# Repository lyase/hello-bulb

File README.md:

as of october 2015
I think  master branch is broken  with
device:  device_plan.pro
firmware: /home/ubsafder/work/hello-bulb/firmware/usbtiny-1.7/usb-device-standalone-firmware/

so i am making a new branch now based on the work https://www.obdev.at/products/vusb/prjdetail.php?pid=0
the new board is power-switch.pro
and the firmware are found in /PowerSwitchobdev/
to be tested in real world

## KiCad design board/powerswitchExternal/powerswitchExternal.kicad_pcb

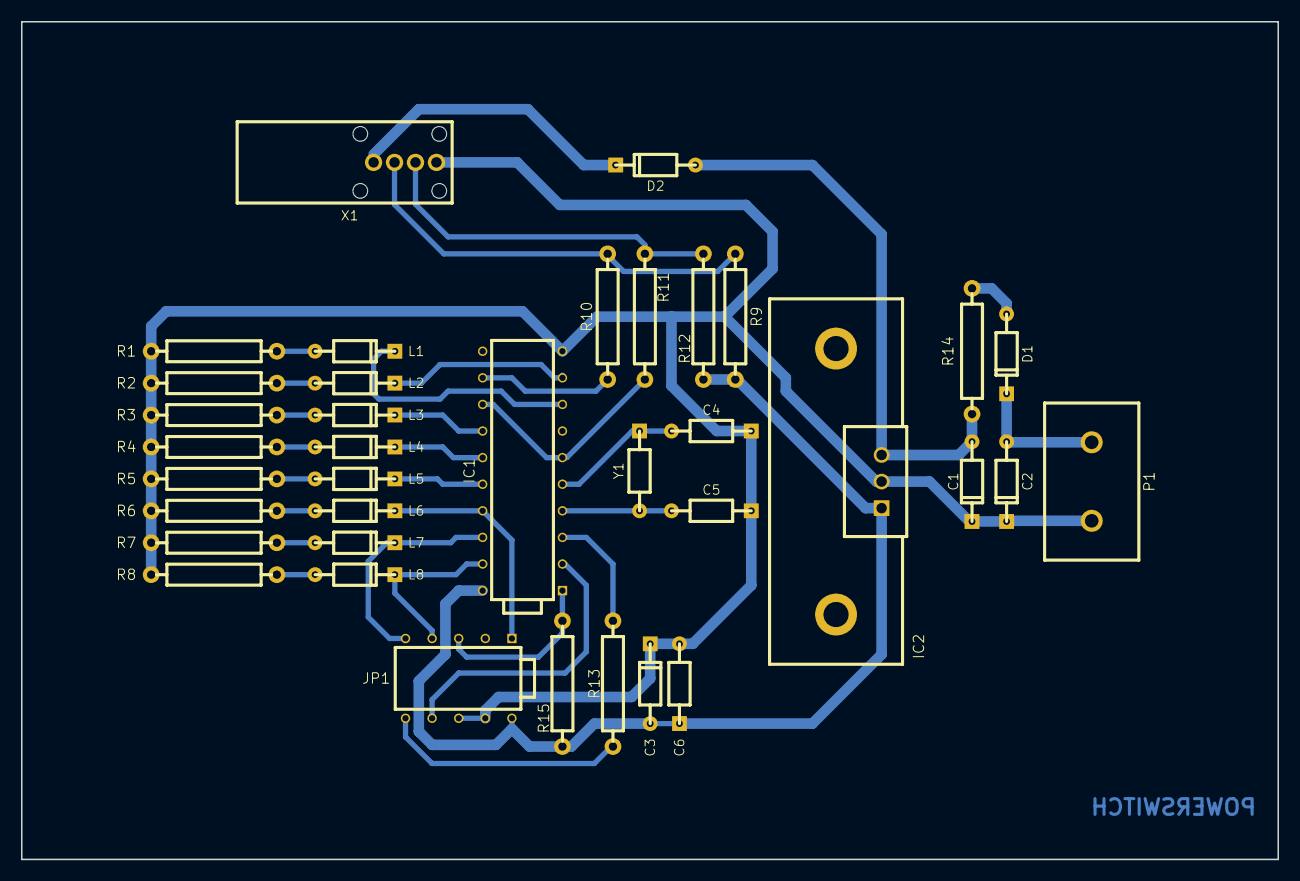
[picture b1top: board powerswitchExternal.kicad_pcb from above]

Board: 2 copper layers, 120.0 x 80.0 mm, 37 parts (0 on the bottom side), 32 nets.

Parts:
C1: 10u/16V; PT-DO35
C2: 1000u/16V; PT-DO35
C3: 2u2/16V; PT-DO35
C4, C5: 15p; PT-CAP
C6: 100n; PT-CAP
D1, D2: 1N4148; PT-DO35
IC1: AT90S2313-P; PT-PDIP20
IC2: LE35CZ; PT-TO220AB
JP1: CONN_02X05; PT-PDIP10
L1, L2, L3, L4, L5, L6, L7, L8: LED; PT-DO35
P1: 12V DC; PT-CONN2-7.5mm
R1, R2, R3, R4, R5, R6, R7, R8: 1K; R7
R9: 1K5; R7
R10, R11: 68R; R7
R12: 1M; R7
R13, R15: 10K; R7
R14: 330R; R7
X1: USB; PT-TE292336
Y1: 12MHz; PT-CAP

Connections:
GND: C1.2, C2.2, C3.2, C4.2, C5.2, C6.1, IC1.10, IC2.2, JP1.4, JP1.6, P1.2, R1.2, R2.2, R3.2, R4.2, R5.2, R6.2, R7.2, R8.2, X1.4
unnamed: C1.1, D2.1, IC2.3, R14.2
unnamed: C2.1, D1.2, P1.1
unnamed: C3.1, C6.2, IC1.20, IC2.1, JP1.2, R9.1, R12.1, R15.1
unnamed: C4.1, IC1.5, Y1.2
unnamed: C5.1, IC1.4, Y1.1
unnamed: D1.1, R14.1
unnamed: D2.2, X1.1
unnamed: IC1.1, JP1.5, R15.2
unnamed: IC1.2, JP1.8
unnamed: IC1.3, R13.1
unnamed: IC1.8, L1.2
unnamed: IC1.9, L2.2
unnamed: IC1.12, R10.1
unnamed: IC1.6, IC1.13, R11.1
unnamed: IC1.14, L3.2
unnamed: IC1.15, L4.2
unnamed: IC1.16, L5.2
unnamed: IC1.17, JP1.1, L6.2
unnamed: IC1.18, JP1.9, L7.2
unnamed: IC1.19, JP1.7, L8.2
unnamed: JP1.10, R13.2
unnamed: L1.1, R1.1
unnamed: L2.1, R2.1
unnamed: L3.1, R3.1
unnamed: L4.1, R4.1
unnamed: L5.1, R5.1
unnamed: L6.1, R6.1
unnamed: L7.1, R7.1
unnamed: L8.1, R8.1
unnamed: R9.2, R10.2, X1.2
unnamed: R11.2, R12.2, X1.3

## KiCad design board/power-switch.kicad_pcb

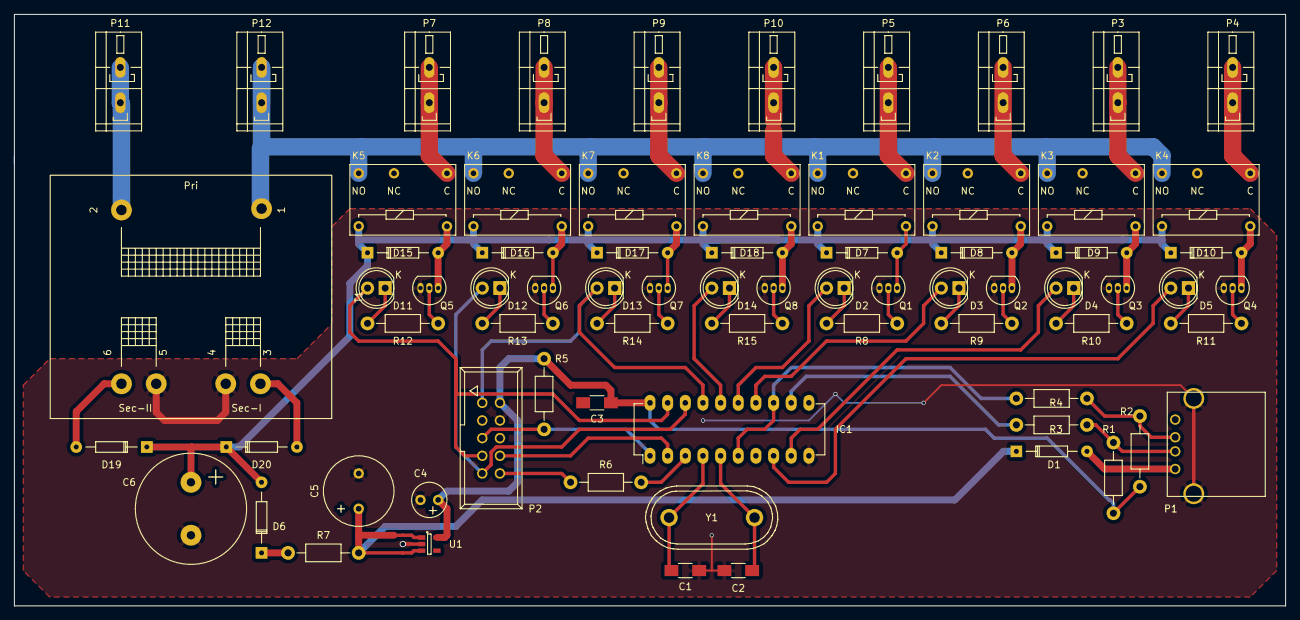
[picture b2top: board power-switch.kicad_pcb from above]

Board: 2 copper layers, 182.9 x 85.1 mm, 73 parts (0 on the bottom side), 60 nets.

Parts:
C1, C2, C3: 15pF; C_1206_HandSoldering
C4: 2u2/16V; Elko_vert_11x5mm_RM2.5
C5: 10uF/16V; Elko_vert_20x10mm_RM5
C6: 1000uF/16V; Elko_vert_31.5x16mm_RM7.5
D1, D6, D7, D8, D9, D10, D15, D16, D17, D18: 1N4148; Diode_DO-35_SOD27_Horizontal_RM10
D2, D3, D4, D5, D11, D12, D13, D14: LED; LED-5MM
D19, D20: 1N4004; Diode_DO-35_SOD27_Horizontal_RM10
IC1: AT90S2313-P; DIP-20_W7.62mm_LongPads
K1, K2, K3, K4, K5, K6, K7, K8: RELAY; Relay_SPDS_OMRON-G6E
P1: USB_A
P2: CONN_02X05; VASCH5x2
P3, P4, P5, P6, P7, P8, P9, P10, P11, P12: TEST; TerminalBlock_WAGO-236_2Stift_RM5mm_1pol
Q1, Q2, Q3, Q4, Q5, Q6, Q7, Q8: BC547; TO-92_Inline_Narrow_Oval
R1: 1K5; Resistor_Horizontal_RM10mm
R2: 1M; Resistor_Horizontal_RM10mm
R3, R4: 68R; Resistor_Horizontal_RM10mm
R5, R6: 10K; Resistor_Horizontal_RM10mm
R7: 330R; Resistor_Horizontal_RM10mm
R8, R9, R10, R11, R12, R13, R14, R15: 1K; Resistor_Horizontal_RM10mm
T1: TRANSFO2; Trafo_CHK-EI38-3VA_2xSec
U1: TLV70235DBV; SOT-23-5
Y1: Crystal; Crystal_HC48-U_Vertical

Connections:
GND: C1.1, C2.1, C4.2, C5.2, C6.2, IC1.10, P1.5, P2.4, P2.6, Q1.3, Q2.3, Q3.3, Q4.3, Q5.3, Q6.3, Q7.3, Q8.3, T1.4, T1.5, U1.2
unnamed: C1.2, IC1.4, Y1.1
unnamed: C2.2, IC1.5, Y1.2
unnamed: C5.1, D1.1, R7.1, U1.1, U1.3
unnamed: C6.1, D6.2, D7.1, D8.1, D9.1, D10.1, D15.1, D16.1, D17.1, D18.1, D19.1, D20.1, K1.8, K2.8, K3.8, K4.8, K5.8, K6.8, K7.8, K8.8
unnamed: D1.2, P1.1
unnamed: D2.1, R8.2
unnamed: D3.1, R9.2
unnamed: D4.1, R10.2
unnamed: D5.1, R11.2
unnamed: D6.1, R7.2
unnamed: D7.2, K1.9, Q1.1
unnamed: D8.2, K2.9, Q2.1
unnamed: D9.2, K3.9, Q3.1
unnamed: D10.2, K4.9, Q4.1
unnamed: D11.1, R12.2
unnamed: D12.1, R13.2
unnamed: D13.1, R14.2
unnamed: D14.1, R15.2
unnamed: D15.2, K5.9, Q5.1
unnamed: D16.2, K6.9, Q6.1
unnamed: D17.2, K7.9, Q7.1
unnamed: D18.2, K8.9, Q8.1
unnamed: D19.2, T1.6
unnamed: D20.2, T1.3
unnamed: IC1.1, P2.5, R5.2
unnamed: IC1.2, P2.8
unnamed: IC1.3, R6.1
unnamed: IC1.12, R3.1
unnamed: IC1.6, IC1.13, R4.1
unnamed: K1.1, K2.1, K3.1, K4.1, K5.1, K6.1, K7.1, K8.1, P12.1, T1.1
unnamed: K1.5, P5.1
unnamed: K2.5, P6.1
unnamed: K3.5, P3.1
unnamed: K4.5, P4.1
unnamed: K5.5, P7.1
unnamed: K6.5, P8.1
unnamed: K7.5, P9.1
unnamed: K8.5, P10.1
unnamed: P1.2, R1.2, R3.2
unnamed: P1.3, R2.2, R4.2
unnamed: P2.10, R6.2
unnamed: P11.1, T1.2
unnamed: Q1.2, R8.1
unnamed: Q2.2, R9.1
unnamed: Q3.2, R10.1
unnamed: Q4.2, R11.1
unnamed: Q5.2, R12.1
unnamed: Q6.2, R13.1
unnamed: Q7.2, R14.1
unnamed: Q8.2, R15.1
PB2: D3.2, IC1.14
PB3: D2.2, IC1.15
PB4: D14.2, IC1.16
PB5: D13.2, IC1.17, P2.1
PB6: D12.2, IC1.18, P2.9
PB7: D11.2, IC1.19, P2.7
PD4: D5.2, IC1.8
PD5: D4.2, IC1.9
VCC: C3.1, C4.1, IC1.20, P2.2, R1.1, R2.1, R5.1, U1.5

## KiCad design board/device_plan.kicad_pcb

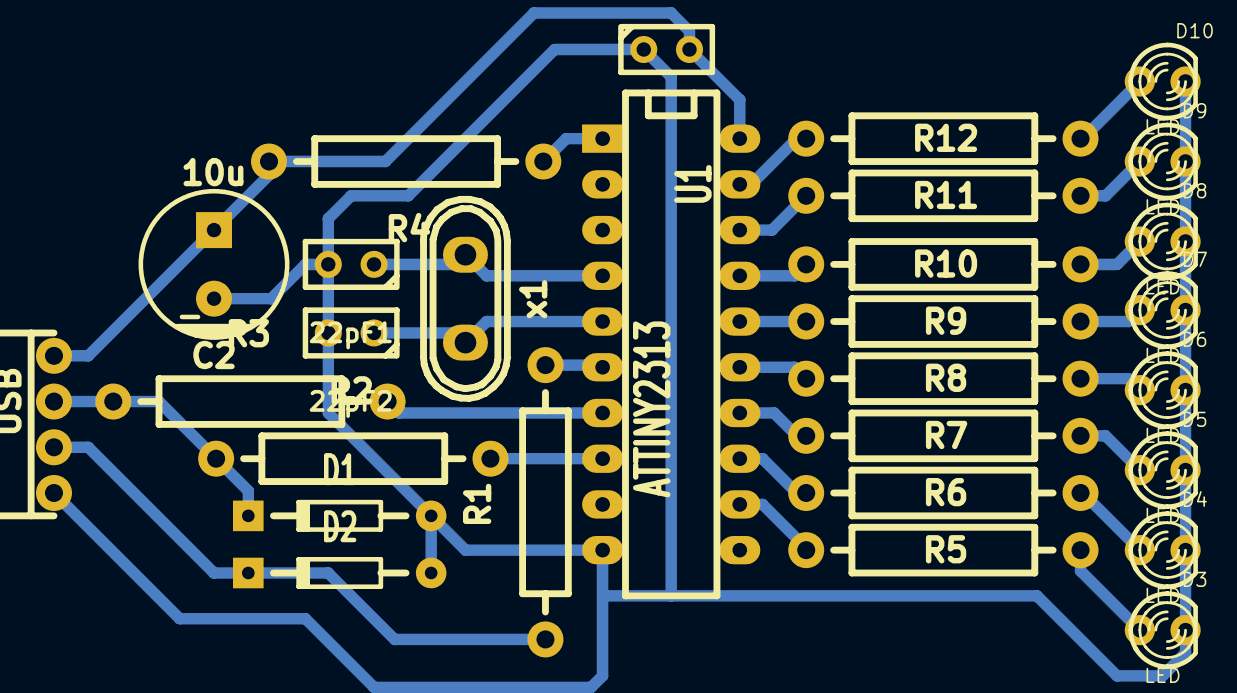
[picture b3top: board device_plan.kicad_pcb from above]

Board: 2 copper layers, 29 parts (0 on the bottom side), 26 nets.

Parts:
22pF1, 22pF2: C; Capacitor3MMDiscRM2.5
C1: 100n; Capacitor3MMDiscRM2.5
C2: 10u; Capacitor8x13RM3.8
D1, D2: 3.6V; Diode_DO-35_SOD27_Horizontal_RM10
D3, D4, D5, D6, D7, D8, D9, D10: LED; LED-3MM
J1: USB; KK04_MC
R1, R2: 68 ohms; Resistor_Horizontal_RM15mm
R3: 1500 ohms; Resistor_Horizontal_RM15mm
R4: 10 kohms; Resistor_Horizontal_RM15mm
R5, R6, R7, R8, R9, R10, R11, R12: 47 ohms; Resistor_Horizontal_RM15mm
U1: ATTINY2313; DIP-20__300_ELL
x1: 12M; Crystal_HC50-U_Vertical

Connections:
GND: 22pF1.2, 22pF2.2, C1.1, C2.2, D1.1, D2.1, D3.2, D4.2, D5.2, D6.2, D7.2, D8.2, D9.2, D10.2, J1.4, U1.10
unnamed: 22pF1.1, U1.4, x1.1
unnamed: 22pF2.1, U1.5, x1.2
unnamed: D1.2, J1.2, R2.1, R3.1
unnamed: D2.2, J1.3, R1.1
unnamed: D3.1, R5.1
unnamed: D4.1, R6.1
unnamed: D5.1, R7.1
unnamed: D6.1, R8.1
unnamed: D7.1, R9.1
unnamed: D8.1, R10.1
unnamed: D9.1, R11.1
unnamed: D10.1, R12.1
unnamed: R1.2, U1.6
unnamed: R2.2, U1.8
unnamed: R3.2, U1.7
unnamed: R4.1, U1.1
unnamed: R5.2, U1.12
unnamed: R6.2, U1.13
unnamed: R7.2, U1.14
unnamed: R8.2, U1.15
unnamed: R9.2, U1.16
unnamed: R10.2, U1.17
unnamed: R11.2, U1.18
unnamed: R12.2, U1.19
VCC: C1.2, C2.1, J1.1, R4.2, U1.20

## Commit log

2014-07-07 Create gh-pages branch via GitHub
2014-07-08 initial edit
2014-07-08 introduce scientific wild guess for board design
2014-07-08 fix missing zener diodes for usb specs
2014-07-16 include footPrints
2014-07-16 initial firmware
2014-07-16 get firmware to compile. updgraded to usbtiny-1.7 as few files of 1.4 may be broken empty !!
2014-07-17 Reorganized schematic. Fixed input zener errors.
2014-07-19 Modified schematic according to project
2014-07-19 Assigns footprints, rough placement on board (new board file)
2014-07-19 add firmware files
2014-07-19 add missing MakeFile for usb-device-firmware
2014-07-19 add firmware version usbtiny 1.4
2014-07-19 Laid traces on pcb. Added .gitignore.
2014-07-21 refactoring
2014-08-11 correct bug for 8 bit controler
2014-08-15 add script to build latest kicad from source
2014-08-17 update index page
2015-10-04 restarted with obdev version as base project kicad files power-switch.pro are rebuild accordingly device_plan.pro is depreceated todo : build & test this power-switch version
2015-10-06 documenting the start f a new branch
2015-10-15 base PowerSwitch solution only +kicad board from zia
2015-10-15 include kicad files for board
2016-01-16 remove duplicate software folder
